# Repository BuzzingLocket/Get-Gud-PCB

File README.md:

# Get-Gud-PCB
Getting good at PCB
Objectives: Design a PCB with an RP2040 which includes ICs to read 9-axis of sensor data (yaw, pitch, roll, acceleration, gyro, etc)m barometric pressure and temperature.

Design requirements:
- USB-C must be included. Pay attention to VBUS as that’s your power input
- RP2040
- 9-axis measurement
- Pressure sensing
- Temperature sensing
- LCSC/JLC part # included for all symbols used (i.e C2040)
- Bonus points for readable schematics and compact layout!!!!

Using a ICM 20948 IC for 9-axis detection

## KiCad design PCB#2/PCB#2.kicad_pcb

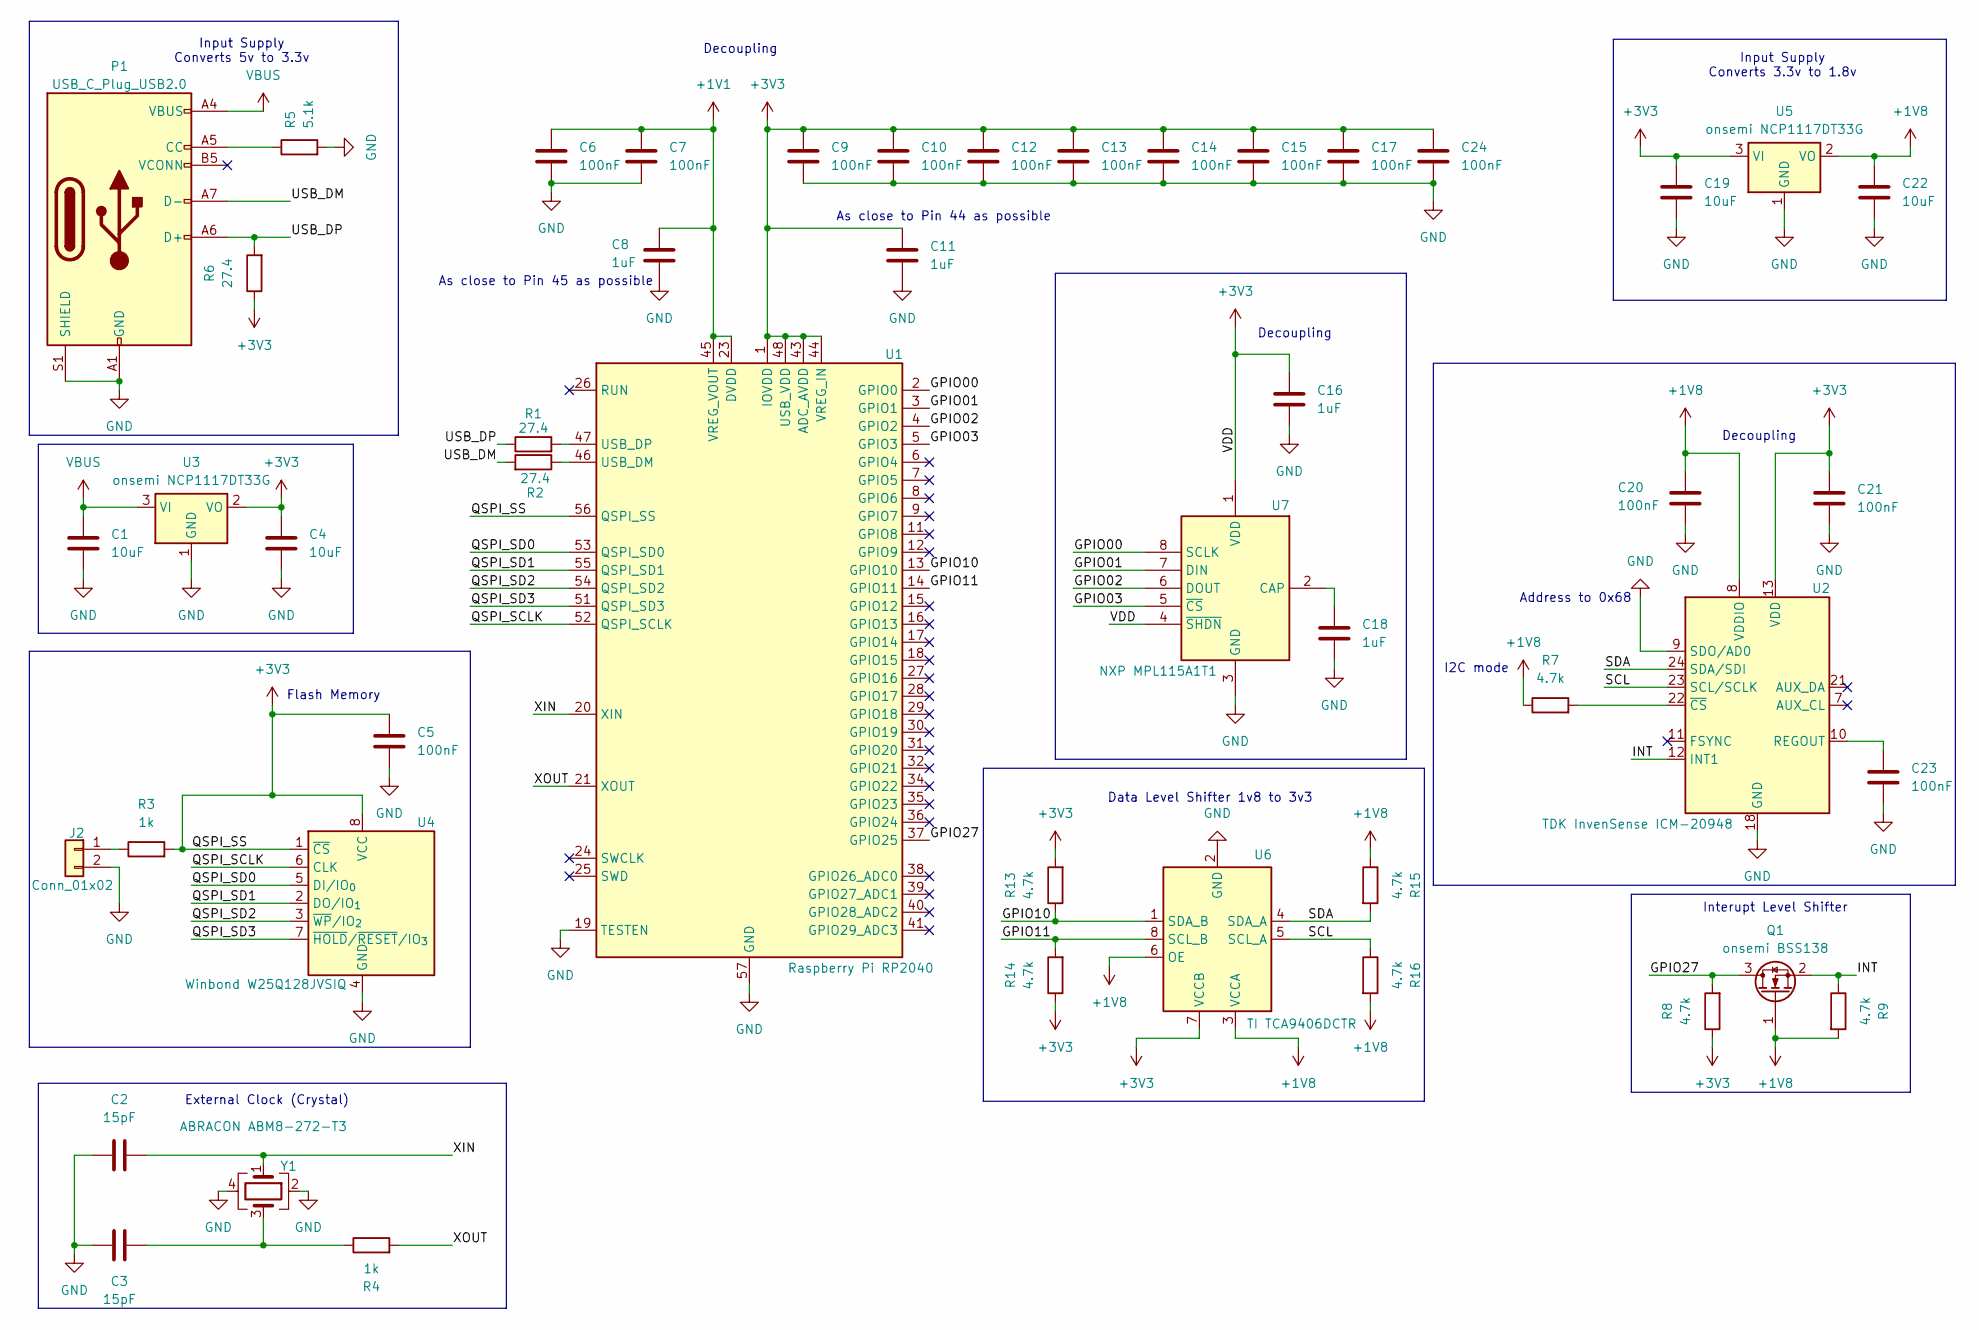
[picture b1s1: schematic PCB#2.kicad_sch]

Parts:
C1, C4, C19, C22: 10uF; C_0603_1608Metric
C2, C3: 15pF; C_0603_1608Metric
C5, C6, C7, C9, C10, C12, C13, C14, C15, C17, C20, C21, C23, C24: 100nF; C_0603_1608Metric
C8, C11, C16, C18: 1uF; C_0603_1608Metric
J2: Conn_01x02; PinHeader_1x02_P2.54mm_Vertical
P1: USB_C_Plug_USB2.0; USB_C_Receptacle_HRO_TYPE-C-31-M-12
Q1: onsemi BSS138; SOT-23
R1, R2, R6: 27.4; R_0603_1608Metric
R3, R4: 1k; R_0603_1608Metric
R5: 5.1k; R_0603_1608Metric
R7, R8, R9, R13, R14, R15, R16: 4.7k; R_0603_1608Metric
U1: Raspberry Pi RP2040; QFN-56-1EP_7x7mm_P0.4mm_EP3.2x3.2mm
U2: TDK InvenSense ICM-20948; InvenSense_QFN-24_3x3mm_P0.4mm
U3, U5: onsemi NCP1117DT33G; SOT-223-3_TabPin2
U4: Winbond W25Q128JVSIQ; SOIC-8_5.3x5.3mm_P1.27mm
U6: TI TCA9406DCTR; VSSOP-8_3x3mm_P0.65mm
U7: NXP MPL115A1T1; NXP_LGA-8_3x5mm_P1.25mm_H1.2mm
Y1: ABRACON ABM8-272-T3; Crystal_SMD_Abracon_ABM8G-4Pin_3.2x2.5mm

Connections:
+1V1: C6.1, C7.1, C8.1, U1.23 (DVDD), U1.45 (VREG_VOUT), U1.50 (DVDD)
+1V8: C20.1, C22.1, Q1.1 (G), R7.1, R9.2, R15.1, R16.2, U2.8 (VDDIO), U5.2 (VO), U6.3 (VCCA), U6.6 (OE)
+3V3: C4.1, C5.1, C9.1, C10.1, C11.1, C12.1, C13.1, C14.1, C15.1, C16.1, C17.1, C19.1, C21.1, C24.1, R3.2, R6.1, R8.1, R13.2, R14.1, U1.1 (IOVDD), U1.10 (IOVDD), U1.22 (IOVDD), U1.33 (IOVDD), U1.42 (IOVDD), U1.43 (ADC_AVDD), U1.44 (VREG_IN), U1.48 (USB_VDD), U1.49 (IOVDD), U1.56 (QSPI_SS), U2.13 (VDD), U3.2 (VO), U4.1 (~CS), U4.8 (VCC), U5.3 (VI), U6.7 (VCCB), U7.1 (VDD), U7.4 (~SHDN)
/GPIO00: U1.2 (GPIO0), U7.8 (SCLK)
/GPIO01: U1.3 (GPIO1), U7.7 (DIN)
/GPIO02: U1.4 (GPIO2), U7.6 (DOUT)
/GPIO03: U1.5 (GPIO3), U7.5 (~CS)
/GPIO10: R13.1, U1.13 (GPIO10), U6.1 (SDA_B)
/GPIO11: R14.2, U1.14 (GPIO11), U6.8 (SCL_B)
/GPIO27: Q1.3 (D), R8.2, U1.37 (GPIO25)
/INT: Q1.2 (S), R9.1, U2.12 (INT1)
/QSPI_SCLK: U1.52 (QSPI_SCLK), U4.6 (CLK)
/QSPI_SD0: U1.53 (QSPI_SD0), U4.5 (DI/IO_{0})
/QSPI_SD1: U1.55 (QSPI_SD1), U4.2 (DO/IO_{1})
/QSPI_SD2: U1.54 (QSPI_SD2), U4.3 (~WP/IO_{2})
/QSPI_SD3: U1.51 (QSPI_SD3), U4.7 (~HOLD/~RESET/IO_{3})
/SCL: R16.1, U2.23 (SCL/SCLK), U6.5 (SCL_A)
/SDA: R15.2, U2.24 (SDA/SDI), U6.4 (SDA_A)
/USB_DM: P1.A7 (D-), R2.2
/USB_DP: P1.A6 (D+), R1.1, R6.2
/XIN: C2.1, U1.20 (XIN), Y1.1
/XOUT: R4.2, U1.21 (XOUT)
GND: C1.2, C2.2, C3.2, C4.2, C5.2, C6.2, C7.2, C8.2, C9.2, C10.2, C11.2, C12.2, C13.2, C14.2, C15.2, C16.2, C17.2, C18.2, C19.2, C20.2, C21.2, C22.2, C23.2, C24.2, J2.2, P1.A1 (GND), P1.A12 (GND), P1.B1 (GND), P1.B12 (GND), P1.S1 (SHIELD), R5.2, U1.19 (TESTEN), U1.57 (GND), U2.9 (SDO/AD0), U2.18 (GND), U2.20 (GND), U3.1 (GND), U4.4 (GND), U5.1 (GND), U6.2 (GND), U7.3 (GND), Y1.2, Y1.4
unnamed: C3.1, R4.1, Y1.3
unnamed: J2.1, R3.1
unnamed: P1.A5 (CC), R5.1
unnamed: R2.1, U1.46 (USB_DM)
unnamed: R1.2, U1.47 (USB_DP)
unnamed: C23.1, U2.10 (REGOUT)
unnamed: R7.2, U2.22 (~CS)
unnamed: C18.1, U7.2 (CAP)
VBUS: C1.1, P1.A4 (VBUS), P1.A9 (VBUS), P1.B4 (VBUS), P1.B9 (VBUS), U3.3 (VI)

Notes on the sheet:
Decoupling
Flash Memory
Address to 0x68
As close to Pin 45 as possible
Input Supply Converts 3.3v to 1.8v
Input Supply Converts 5v to 3.3v
Data Level Shifter 1v8 to 3v3
I2C mode
External Clock (Crystal)
Interupt Level Shifter
As close to Pin 44 as possible

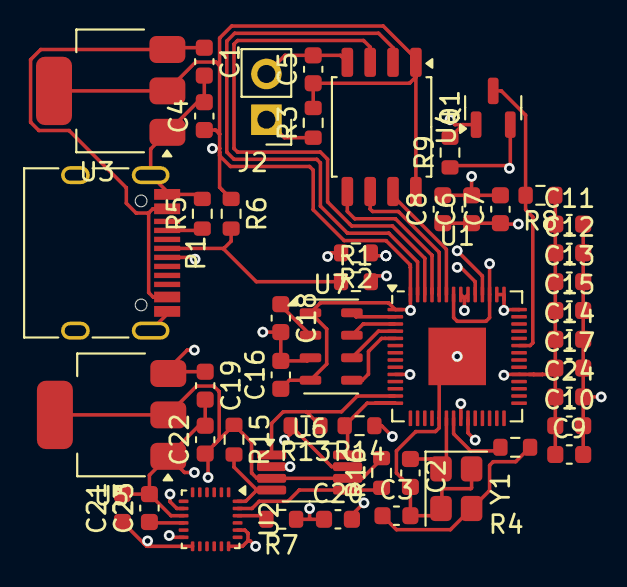
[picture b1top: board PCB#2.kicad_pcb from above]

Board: 4 copper layers, 48 parts (0 on the bottom side), 32 nets.

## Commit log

2025-09-26 Rename DS-000189-ICM-20948-v1.6.pdf to ICM-20948-Datasheet.pdf
2025-10-01 Add files via upload
    Fixed pull ups
